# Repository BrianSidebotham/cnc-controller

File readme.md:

# CNC Controller

This CNC controller is an expansion board for LinuxCNC. See the [electronics](electronics/readme.md) section for the RPi GPIO expansion board suitable for use with LinuxCNC using the [configuration](linuxcnc-configuration/denford-orac-rpi/readme.md).

The PCB is an opto-isolation IO expansion board featuring:

- 16 Opto-isolated outputs (With indicator LED)
- 8 opto-isolated inputs (With indicator LED)
- 2 0-10V analogue outputs connected to two of the opto-isolated outputs

## KiCAD Parts Library

This project relies on my KiCAD parts library. So you will need to also clone a copy of my
[KiCAD parts library](https://github.com/BrianSidebotham/kicad-parts).

Then, you can tell KiCAD where to find the parts library by creating a new environment
variable called `KICAD_BJS_KICAD_PARTS` and set the value to the path to the parts library.

If you get the value or variable name wrong you'll see a lot of missing symbols in the
project.

## Build LinuxCNC

You can go ahead and download the LinuxCNC Distribution or else you can build yourself an up-to-date version.

In order to get an up-to-date version, download the LinuxCNC RPi image and write it to an SD Card.

Boot the card and then do the following to update the LinuxCNC package:

```shell
$ wget https://www.linuxcnc.org/dists/buster/2.8-rtpreempt/binary-armhf/linuxcnc-uspace_2.8.4_armhf.deb
$ sudo dpkg -i ./linuxcnc-uspace_2.8.4_armhf.deb
```

## Future Buildroot

In order to build an OS specifically for LinuxCNC you can use the following instructions:

>**WARNING**: These instructions are for future use, do not use yet.

```shell
$ wget https://buildroot.org/downloads/buildroot-2022.02.5.tar.gz
$ tar xf buildroot-2022.02.5.tar.gz
$ cd buildroot-2022.02.5
$ make raspberrypi4_64_defconfig
```

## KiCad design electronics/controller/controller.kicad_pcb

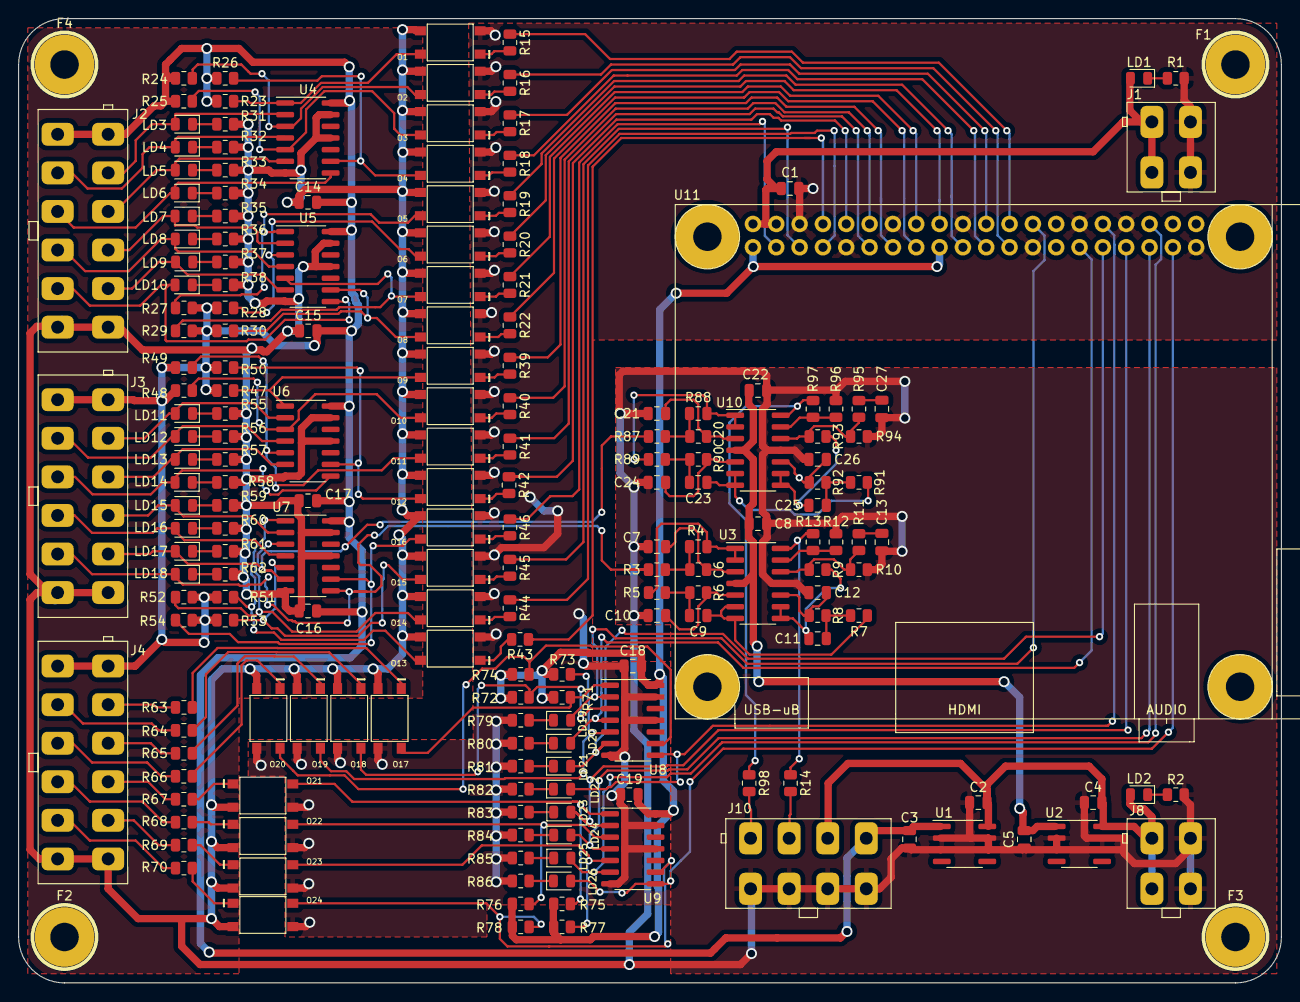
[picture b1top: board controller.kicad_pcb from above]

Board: 2 copper layers, 137.5 x 105.0 mm, 196 parts (0 on the bottom side), 157 nets.

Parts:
C1, C2, C3, C4, C5, C8, C14, C15, C16, C17, C18, C19, C22: 100n; C_0805_2012Metric
C6, C7, C9, C10, C11, C12, C13, C20, C21, C23, C24, C25, C26, C27: 1u; C_0805_2012Metric
F1, F2, F3, F4: M3
J1, J8: TEVALULOK4W; te-connectivity_val-u-lok_vertical_4_1586768-4
J2, J3, J4: TEVALULOK12W; te-connectivity_val-u-lok_vertical_12_1-1586768-2
J10: TEVALULOK8W; te-connectivity_val-u-lok_vertical_8_1586768-8
LD1, LD2, LD3, LD4, LD5, LD6, LD7, LD8, LD9, LD10, LD11, LD12, LD13, LD14, LD15, LD16, LD17, LD18, LD19, LD20, LD21, LD22, LD23, LD24, LD25, LD26: LED; LED_0805_2012Metric
O1, O2, O3, O4, O5, O6, O7, O8, O9, O10, O11, O12, O13, O14, O15, O16, O17, O18, O19, O20, O21, O22, O23, O24: VOM617A-4T; VOMOPTO
R1: RESISTOR; R_0805_2012Metric
R2: 2k2; R_0805_2012Metric
R3, R4, R5, R6, R7, R8, R9, R87, R88, R89, R90, R91, R92, R93: 68k; R_0805_2012Metric
R10, R12, R94, R96: 1k5; R_0805_2012Metric
R11, R13, R95, R97: 120k; R_0805_2012Metric
R14, R31, R32, R33, R34, R35, R36, R37, R38, R55, R56, R57, R58, R59, R60, R61, R62, R79, R80, R81, R82, R83, R84, R85, R86, R98: 330R; R_0805_2012Metric
R15, R16, R17, R18, R19, R20, R21, R22, R39, R40, R41, R42, R43, R44, R45, R46, R63, R64, R65, R66, R67, R68, R69, R70: 680R; R_0805_2012Metric
R23, R24, R25, R26, R27, R28, R29, R30, R47, R48, R49, R50, R51, R52, R53, R54, R71, R72, R73, R74, R75, R76, R77, R78: 1k; R_0805_2012Metric
U1: 78L05SMD; SOIC-8_3.9x4.9mm_P1.27mm
U2: 78L10SMD; SOIC-8_3.9x4.9mm_P1.27mm
U3, U10: MC33204; SOIC-14_3.9x8.7mm_P1.27mm
U4, U5, U6, U7, U8, U9: 74HC14; SOIC-14_3.9x8.7mm_P1.27mm
U11: RPI40PIN; rpi-40pin

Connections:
+10V: C5.2, C8.2, C22.2, U2.1 (VO), U3.4 (VCC), U10.4 (VCC)
+12V: C2.2, C4.2, J8.1, J8.2, J10.5, LD2.2, U1.8 (VIN), U2.8 (VIN)
/0-10V-CH1: J10.1, R98.2
/0-10V-CH2: J10.3, R14.2
/IN1: J4.3, R63.1
/IN2: J4.4, R64.1
/IN3: J4.5, R65.1
/IN4: J4.6, R66.1
/IN5: J4.7, R67.1
/IN6: J4.8, R68.1
/IN7: J4.9, R69.1
/IN8: J4.10, R70.1
/OUT1: J2.3, LD3.2, U4.2
/OUT2: J2.4, LD4.2, U4.4
/OUT3: J2.5, LD5.2, U4.6
/OUT4: J2.6, LD6.2, U4.8
/OUT5: J2.7, LD7.2, U5.2
/OUT6: J2.8, LD8.2, U5.4
/OUT7: J2.9, LD9.2, U5.6
/OUT8: J2.10, LD10.2, U5.8
/OUT9: J3.3, LD11.2, U6.2
/OUT10: J3.4, LD12.2, U6.4
/OUT11: J3.5, LD13.2, U6.6
/OUT12: J3.6, LD14.2, U6.8
/OUT13: J3.7, LD15.2, U7.2
/OUT14: J3.8, LD16.2, U7.4
/OUT15: J3.9, LD17.2, R87.1, U7.6
/OUT16: J3.10, LD18.2, R3.1, U7.8
/RPIIN1: LD19.2, U8.2, U11.26 (GPIO7)
/RPIIN2: LD20.2, U8.4, U11.29 (GPIO5)
/RPIIN3: LD21.2, U8.6, U11.31 (GPIO6)
/RPIIN4: LD22.2, U8.8, U11.32 (GPIO12)
/RPIIN5: LD23.2, U9.2, U11.33 (GPIO13)
/RPIIN6: LD24.2, U9.4, U11.35 (GPIO19)
/RPIIN7: LD25.2, U9.6, U11.36 (GPIO16)
/RPIIN8: LD26.2, U9.8, U11.37 (GPIO26)
/RPIOUT1: R15.1, U11.24 (GPIO8)
/RPIOUT2: R16.1, U11.23 (GPIO11)
/RPIOUT3: R17.1, U11.22 (GPIO25)
/RPIOUT4: R18.1, U11.21 (GPIO9)
/RPIOUT5: R19.1, U11.19 (GPIO10)
/RPIOUT6: R20.1, U11.18 (GPIO24)
/RPIOUT7: R21.1, U11.16 (GPIO23)
/RPIOUT8: R22.1, U11.15 (GPIO22)
/RPIOUT9: R39.1, U11.13 (GPIO27)
/RPIOUT10: R40.1, U11.12 (GPIO18)
/RPIOUT11: R41.1, U11.11 (GPIO17)
/RPIOUT12: R42.1, U11.10 (GPIO15)
/RPIOUT13: R43.1, U11.8 (GPIO14)
/RPIOUT14: R44.1, U11.7 (GPIO4)
/RPIOUT15: R45.1, U11.5 (GPIO3)
/RPIOUT16: R46.1, U11.3 (GPIO2)
/rpiconnectivity/3V3: C18.2, C19.2, R71.2, R72.2, R73.2, R74.2, R75.2, R76.2, R77.2, R78.2, U8.14 (VCC), U9.14 (VCC), U11.1 (3V3), U11.17 (3V3)
GND: C1.1, C18.1, C19.1, J1.3, J1.4, O1.2, O2.2, O3.2, O4.2, O5.2, O6.2, O7.2, O8.2, O9.2, O10.2, O11.2, O12.2, O13.2, O14.2, O15.2, O16.2, O17.3, O18.3, O19.3, O20.3, O21.3, O22.3, O23.3, O24.3, R1.2, R79.2, R80.2, R81.2, R82.2, R83.2, R84.2, R85.2, R86.2, U8.7 (GND), U8.11, U8.13, U9.7 (GND), U9.11, U9.13, U11.6 (GND), U11.9 (GND), U11.14 (GND), U11.20 (GND), U11.25 (GND), U11.30 (GND), U11.34 (GND), U11.39 (GND)
unnamed: C6.1, R5.1, U3.1, U3.2 (-)
unnamed: C6.2, R3.2, R4.1
unnamed: C7.2, R4.2, U3.3 (+)
unnamed: C9.1, R7.1, U3.6 (-), U3.7
unnamed: C9.2, R5.2, R6.1
unnamed: C10.2, R6.2, U3.5 (+)
unnamed: C11.1, R9.1, U3.8, U3.9 (-)
unnamed: C11.2, R7.2, R8.1
unnamed: C12.2, R8.2, U3.10 (+)
unnamed: C13.2, R11.2
unnamed: C20.1, R89.1, U10.1, U10.2 (-)
unnamed: C20.2, R87.2, R88.1
unnamed: C21.2, R88.2, U10.3 (+)
unnamed: C23.1, R91.1, U10.6 (-), U10.7
unnamed: C23.2, R89.2, R90.1
unnamed: C24.2, R90.2, U10.5 (+)
unnamed: C25.1, R93.1, U10.8, U10.9 (-)
unnamed: C25.2, R91.2, R92.1
unnamed: C26.2, R92.2, U10.10 (+)
unnamed: C27.2, R95.2
unnamed: LD1.1, R1.1
unnamed: LD2.1, R2.1
unnamed: LD3.1, R31.1
unnamed: LD4.1, R32.1
unnamed: LD5.1, R33.1
unnamed: LD6.1, R34.1
unnamed: LD7.1, R35.1
unnamed: LD8.1, R36.1
unnamed: LD9.1, R37.1
unnamed: LD10.1, R38.1
unnamed: LD11.1, R55.1
unnamed: LD12.1, R56.1
unnamed: LD13.1, R57.1
unnamed: LD14.1, R58.1
unnamed: LD15.1, R59.1
unnamed: LD16.1, R60.1
unnamed: LD17.1, R61.1
unnamed: LD18.1, R62.1
unnamed: LD19.1, R79.1
unnamed: LD20.1, R80.1
unnamed: LD21.1, R81.1
unnamed: LD22.1, R82.1
unnamed: LD23.1, R83.1
unnamed: LD24.1, R84.1
unnamed: LD25.1, R85.1
unnamed: LD26.1, R86.1
unnamed: O1.1, R15.2
unnamed: O1.4, R23.1, U4.1
unnamed: O2.1, R16.2
unnamed: O2.4, R24.1, U4.3
unnamed: O3.1, R17.2
unnamed: O3.4, R25.1, U4.5
unnamed: O4.1, R18.2
unnamed: O4.4, R26.1, U4.9
unnamed: O5.1, R19.2
unnamed: O5.4, R27.1, U5.1
unnamed: O6.1, R20.2
unnamed: O6.4, R28.1, U5.3
unnamed: O7.1, R21.2
unnamed: O7.4, R29.1, U5.5
unnamed: O8.1, R22.2
unnamed: O8.4, R30.1, U5.9
unnamed: O9.1, R39.2
unnamed: O9.4, R47.1, U6.1
unnamed: O10.1, R40.2
unnamed: O10.4, R48.1, U6.3
unnamed: O11.1, R41.2
unnamed: O11.4, R49.1, U6.5
unnamed: O12.1, R42.2
unnamed: O12.4, R50.1, U6.9
unnamed: O13.1, R43.2
unnamed: O13.4, R51.1, U7.1
unnamed: O14.1, R44.2
unnamed: O14.4, R52.1, U7.3
unnamed: O15.1, R45.2
unnamed: O15.4, R53.1, U7.5
unnamed: O16.1, R46.2
unnamed: O16.4, R54.1, U7.9
unnamed: O17.1, R63.2
unnamed: O17.4, R71.1, U8.1
unnamed: O18.1, R64.2
unnamed: O18.4, R72.1, U8.3
unnamed: O19.1, R65.2
unnamed: O19.4, R73.1, U8.5
unnamed: O20.1, R66.2
unnamed: O20.4, R74.1, U8.9
unnamed: O21.1, R67.2
unnamed: O21.4, R75.1, U9.1
unnamed: O22.1, R68.2
unnamed: O22.4, R76.1, U9.3
unnamed: O23.1, R69.2
unnamed: O23.4, R77.1, U9.5
unnamed: O24.1, R70.2
unnamed: O24.4, R78.1, U9.9
unnamed: R9.2, R10.1, R11.1, U3.12 (+)
unnamed: R12.1, R13.1, U3.13 (-)
unnamed: R13.2, R14.1, U3.14
unnamed: R93.2, R94.1, R95.1, U10.12 (+)
unnamed: R96.1, R97.1, U10.13 (-)
unnamed: R97.2, R98.1, U10.14
VCC: C1.2, J1.1, J1.2, LD1.2, U11.2 (5V), U11.4 (5V)
VDD: C3.2, C14.2, C15.2, C16.2, C17.2, J2.1, J2.2, J3.1, J3.2, J4.1, J4.2, J10.7, R23.2, R24.2, R25.2, R26.2, R27.2, R28.2, R29.2, R30.2, R47.2, R48.2, R49.2, R50.2, R51.2, R52.2, R53.2, R54.2, U1.1 (VO), U4.14 (VCC), U5.14 (VCC), U6.14 (VCC), U7.14 (VCC)
VSS: C2.1, C3.1, C4.1, C5.1, C7.1, C8.1, C10.1, C12.1, C13.1, C14.1, C15.1, C16.1, C17.1, C21.1, C22.1, C24.1, C26.1, C27.1, J2.11, J2.12, J3.11, J3.12, J4.11, J4.12, J8.3, J8.4, J10.2, J10.4, J10.6, J10.8, O1.3, O2.3, O3.3, O4.3, O5.3, O6.3, O7.3, O8.3, O9.3, O10.3, O11.3, O12.3, O13.3, O14.3, O15.3, O16.3, O17.2, O18.2, O19.2, O20.2, O21.2, O22.2, O23.2, O24.2, R2.2, R10.2, R12.2, R31.2, R32.2, R33.2, R34.2, R35.2, R36.2, R37.2, R38.2, R55.2, R56.2, R57.2, R58.2, R59.2, R60.2, R61.2, R62.2, R94.2, R96.2, U1.2 (GND), U1.3 (GND), U1.6 (GND), U1.7 (GND), U2.2 (GND), U2.3 (GND), U2.6 (GND), U2.7 (GND), U3.11 (VEE), U4.7 (GND), U4.11, U4.13, U5.7 (GND), U5.11, U5.13, U6.7 (GND), U6.11, U6.13, U7.7 (GND), U7.11, U7.13, U10.11 (VEE)

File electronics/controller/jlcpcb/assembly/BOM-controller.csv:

Comment,Designator,Footprint,LCSC
1u,"C10,C11,C12,C13,C20,C21,C23,C24,C25,C26,C27,C6,C7,C9",C_0805_2012Metric,C28323
100n,"C1,C14,C15,C16,C17,C18,C19,C2,C22,C3,C4,C5,C8",C_0805_2012Metric,C49678
74HC14,"U4,U5,U6,U7,U8,U9",SOIC-14_3.9x8.7mm_P1.27mm,C5605
TEVALULOK4W,J1,te-connectivity_val-u-lok_vertical_4_1586768-4,
TEVALULOK4W,J8,te-connectivity_val-u-lok_vertical_4_1586768-4,
TEVALULOK8W,J10,te-connectivity_val-u-lok_vertical_8_1586768-8,
RESISTOR,R1,R_0805_2012Metric,
2k2,R2,R_0805_2012Metric,
68k,R3,R_0805_2012Metric,
68k,R4,R_0805_2012Metric,
68k,R5,R_0805_2012Metric,
68k,R6,R_0805_2012Metric,
68k,R7,R_0805_2012Metric,
68k,R8,R_0805_2012Metric,
68k,R9,R_0805_2012Metric,
1k5,R10,R_0805_2012Metric,
120k,R11,R_0805_2012Metric,
120k,R13,R_0805_2012Metric,
1k,R23,R_0805_2012Metric,
MC33204,U3,SOIC-14_3.9x8.7mm_P1.27mm,
1k5,R12,R_0805_2012Metric,
VOM617A-4T,O10,VOMOPTO,
VOM617A-4T,O9,VOMOPTO,
78L10SMD,U2,SOIC-8_3.9x4.9mm_P1.27mm,
LED,LD1,LED_0805_2012Metric,
LED,LD2,LED_0805_2012Metric,
LED,LD3,LED_0805_2012Metric,
LED,LD4,LED_0805_2012Metric,
LED,LD10,LED_0805_2012Metric,
LED,LD19,LED_0805_2012Metric,
LED,LD20,LED_0805_2012Metric,
LED,LD21,LED_0805_2012Metric,
LED,LD23,LED_0805_2012Metric,
LED,LD24,LED_0805_2012Metric,
LED,LD25,LED_0805_2012Metric,
LED,LD26,LED_0805_2012Metric,
VOM617A-4T,O13,VOMOPTO,
VOM617A-4T,O14,VOMOPTO,
VOM617A-4T,O16,VOMOPTO,
VOM617A-4T,O17,VOMOPTO,
VOM617A-4T,O19,VOMOPTO,
VOM617A-4T,O20,VOMOPTO,
VOM617A-4T,O21,VOMOPTO,
VOM617A-4T,O23,VOMOPTO,
1k,R26,R_0805_2012Metric,
1k,R28,R_0805_2012Metric,
1k,R30,R_0805_2012Metric,
330R,R34,R_0805_2012Metric,
330R,R35,R_0805_2012Metric,
330R,R36,R_0805_2012Metric,
330R,R37,R_0805_2012Metric,
330R,R38,R_0805_2012Metric,
680R,R39,R_0805_2012Metric,
680R,R40,R_0805_2012Metric,
680R,R41,R_0805_2012Metric,
680R,R42,R_0805_2012Metric,
680R,R43,R_0805_2012Metric,
680R,R44,R_0805_2012Metric,
680R,R45,R_0805_2012Metric,
680R,R46,R_0805_2012Metric,
1k,R47,R_0805_2012Metric,
1k,R48,R_0805_2012Metric,
1k,R49,R_0805_2012Metric,
1k,R50,R_0805_2012Metric,
1k,R51,R_0805_2012Metric,
1k,R52,R_0805_2012Metric,
1k,R53,R_0805_2012Metric,
680R,R63,R_0805_2012Metric,
680R,R64,R_0805_2012Metric,
680R,R65,R_0805_2012Metric,
680R,R68,R_0805_2012Metric,
680R,R69,R_0805_2012Metric,
680R,R70,R_0805_2012Metric,
1k,R71,R_0805_2012Metric,
1k,R73,R_0805_2012Metric,
1k,R74,R_0805_2012Metric,
1k,R75,R_0805_2012Metric,
1k,R76,R_0805_2012Metric,
1k,R77,R_0805_2012Metric,
1k,R78,R_0805_2012Metric,
330R,R79,R_0805_2012Metric,
330R,R80,R_0805_2012Metric,
330R,R81,R_0805_2012Metric,
330R,R82,R_0805_2012Metric,
330R,R83,R_0805_2012Metric,
330R,R84,R_0805_2012Metric,
68k,R88,R_0805_2012Metric,
68k,R89,R_0805_2012Metric,
68k,R90,R_0805_2012Metric,
68k,R91,R_0805_2012Metric,
68k,R92,R_0805_2012Metric,
68k,R93,R_0805_2012Metric,
1k5,R94,R_0805_2012Metric,
120k,R95,R_0805_2012Metric,
1k5,R96,R_0805_2012Metric,
120k,R97,R_0805_2012Metric,
330R,R98,R_0805_2012Metric,
MC33204,U10,SOIC-14_3.9x8.7mm_P1.27mm,
VOM617A-4T,O11,VOMOPTO,
RPI40PIN,U11,rpi-40pin,
330R,R32,R_0805_2012Metric,
330R,R33,R_0805_2012Metric,
330R,R31,R_0805_2012Metric,
VOM617A-4T,O5,VOMOPTO,
VOM617A-4T,O6,VOMOPTO,
VOM617A-4T,O7,VOMOPTO,
VOM617A-4T,O8,VOMOPTO,
680R,R19,R_0805_2012Metric,
680R,R20,R_0805_2012Metric,
680R,R21,R_0805_2012Metric,
680R,R22,R_0805_2012Metric,
1k,R24,R_0805_2012Metric,
1k,R25,R_0805_2012Metric,
1k,R27,R_0805_2012Metric,
1k,R29,R_0805_2012Metric,
LED,LD8,LED_0805_2012Metric,
LED,LD7,LED_0805_2012Metric,
LED,LD6,LED_0805_2012Metric,
TEVALULOK12W,J2,te-connectivity_val-u-lok_vertical_12_1-1586768-2,
LED,LD9,LED_0805_2012Metric,
LED,LD5,LED_0805_2012Metric,
VOM617A-4T,O12,VOMOPTO,
VOM617A-4T,O15,VOMOPTO,
VOM617A-4T,O18,VOMOPTO,
VOM617A-4T,O22,VOMOPTO,
VOM617A-4T,O24,VOMOPTO,
VOM617A-4T,O1,VOMOPTO,
VOM617A-4T,O2,VOMOPTO,
VOM617A-4T,O3,VOMOPTO,
VOM617A-4T,O4,VOMOPTO,
680R,R15,R_0805_2012Metric,
680R,R16,R_0805_2012Metric,
680R,R17,R_0805_2012Metric,
680R,R18,R_0805_2012Metric,
TEVALULOK12W,J3,te-connectivity_val-u-lok_vertical_12_1-1586768-2,
LED,LD12,LED_0805_2012Metric,
LED,LD13,LED_0805_2012Metric,
LED,LD14,LED_0805_2012Metric,
LED,LD15,LED_0805_2012Metric,
LED,LD16,LED_0805_2012Metric,
LED,LD17,LED_0805_2012Metric,
LED,LD18,LED_0805_2012Metric,
330R,R55,R_0805_2012Metric,
330R,R57,R_0805_2012Metric,
330R,R58,R_0805_2012Metric,
330R,R59,R_0805_2012Metric,
330R,R60,R_0805_2012Metric,
330R,R61,R_0805_2012Metric,
330R,R62,R_0805_2012Metric,
LED,LD11,LED_0805_2012Metric,
TEVALULOK12W,J4,te-connectivity_val-u-lok_vertical_12_1-1586768-2,
330R,R56,R_0805_2012Metric,
1k,R54,R_0805_2012Metric,
680R,R66,R_0805_2012Metric,
680R,R67,R_0805_2012Metric,
LED,LD22,LED_0805_2012Metric,
330R,R85,R_0805_2012Metric,
330R,R86,R_0805_2012Metric,
68k,R87,R_0805_2012Metric,
1k,R72,R_0805_2012Metric,
78L05SMD,U1,SOIC-8_3.9x4.9mm_P1.27mm,
330R,R14,R_0805_2012Metric,
M3,F3,M3,
M3,F4,M3,
M3,F2,M3,
M3,F1,M3,

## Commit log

2022-08-20 Update PCB design to nearly finished design.
2022-08-20 PCB zones added and fully routed
2022-08-21 Add JLCPCB fabrication output post order
2022-08-21 Add Denford Orac Linux CNC configuration
2022-09-07 Add user manual for the VFD motor drive
2022-09-08 Update pin direction configuration and mask to match hardware
2022-09-08 Remove and ignore kicad prl files which contain user settings not required for vcs
2022-09-08 Update HAL to align with PCB and connections to denford Orac
2022-09-08 Test using not function to invert limit switches
2022-09-08 Use same pin for both x and z limits
2022-09-08 Use separate limit switches for each axis
2022-09-08 Correct z limit switch debound connection
2022-09-08 Invert the axis enable signals
2022-09-08 Add spindle feedback control and spindle-at-speed settings
2022-09-08 Add spindle-at-speed feedback
2022-09-08 Add UI spindle at speed LED in UI
2022-09-08 Attach spindle speed to detected spindle speed instead of commanded speed
2022-09-08 Use spindle velocity
2022-09-08 Turn RPS to RPM
2022-09-08 Load scale and lowpass for UI calculations
2022-09-08 Add absolute function to threads
2022-09-08 Add functions to threads
2022-09-09 Update EMC VERSION number for the ini file to shut linuxcnc quiet
2022-09-09 Update for acceleration and speed of stepper drivers
2022-09-09 Add a couple more useful manuals
2022-09-09 Update accel settings for axes and traj section
2022-09-13 Update the spindle speed section to simplify the display
2022-09-14 Calculate scale for both stepper motor axis
2022-09-14 Include gmnoccapy macros for lathe wizards
2022-09-14 Start addition of gmoccapy user interface
2022-09-14 Add the lathe macro wizard UI
2022-09-14 Add potential fix to lathemacro ui
2022-09-14 Add missing HALUI in case that fixes the issue
2022-09-14 Update to get new subcroutine path in
2022-09-14 Return normal ini file to axis
2022-09-15 Add logging to lathehandler to see what's going on
2022-09-15 Update lathehandler and the lahtemacro ui to use gtk2
2022-09-15 Update lathehandler.py to an older version to see if it works
2022-09-15 Attach spindle feedback to UI components of gmoccapy
2022-09-15 Update Axis acceleration and velocities
2022-09-15 Update acceleration curves a bit more
2022-09-15 Update some spindle and general lathe settings
2022-09-15 Update the spindle scale preferences
2022-09-15 Add PID control to spindle
2022-09-15 Fix some issues with PID. Partial Fixes
2022-09-15 Update PID section for spindle
2022-09-15 Only use scale.0.out once
2022-09-15 Add P gain
2022-09-15 Update PID to passthrough velocity
2022-09-15 Add original openloop configuration back in
2022-09-15 PID FF0 correction
2022-09-15 Add openloop ini file also
2022-09-15 Make the ini openloop file use the openloop hal
2022-09-15 Fix issue with HAL file
2022-09-26 Rename spindle net
2022-09-26 Add openloop configuration for the spindle
2022-09-26 Add sum2 function to the servo thread
2022-09-26 Add sum2 0 function to servo thread
2022-09-26 First working PID closed loop spindle control
2022-09-27 PID control of spindle fix
2022-09-27 Improve readability of openloop hal
2022-09-27 Update lathe config for near signal UI
2022-09-27 Add RPM based signals to near for spindle speed
2022-10-12 Adjust the output gain of the 0-10V outputs
2022-10-12 Remove var files which should not be in version control
2022-10-12 Ignore all .var and .bak files
2022-10-12 Add spindle enable signal to IO
2022-10-12 Adjust comments in main gmoccapy ini file
2022-10-12 Update readme documentation for the project
2026-02-15 Add new VFD manuals
2026-02-15 Add relay boad datasheet
2026-02-15 Align with previous configuration
2026-02-15 Update to latest LatheMacros
2026-02-15 Update readme and remove old content
2026-02-22 Update general UI preferences
2026-02-22 Add a closed-loop spindle control version HAL
2026-02-26 Correct scaling for new VFD and motor in open loop
2026-02-26 Update to linuxcnc 2.9.8 (#1)
    * Add new VFD manuals
    * Add relay boad datasheet
    * Align with previous configuration
    * Update to latest LatheMacros
    * Update readme and remove old content
    * Update general UI preferences
